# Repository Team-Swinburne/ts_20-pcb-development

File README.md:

# TS_20 PCB Development

This is the official repository for the PCB development of Team Swinburne FSAE 2020

## Installation & Usage

## Contributing
Pull requests are welcome. For major changes, please open an issue first to discuss what you would like to change.

Please make sure to update tests as appropriate.

## License
[MIT](https://choosealicense.com/licenses/mit/)

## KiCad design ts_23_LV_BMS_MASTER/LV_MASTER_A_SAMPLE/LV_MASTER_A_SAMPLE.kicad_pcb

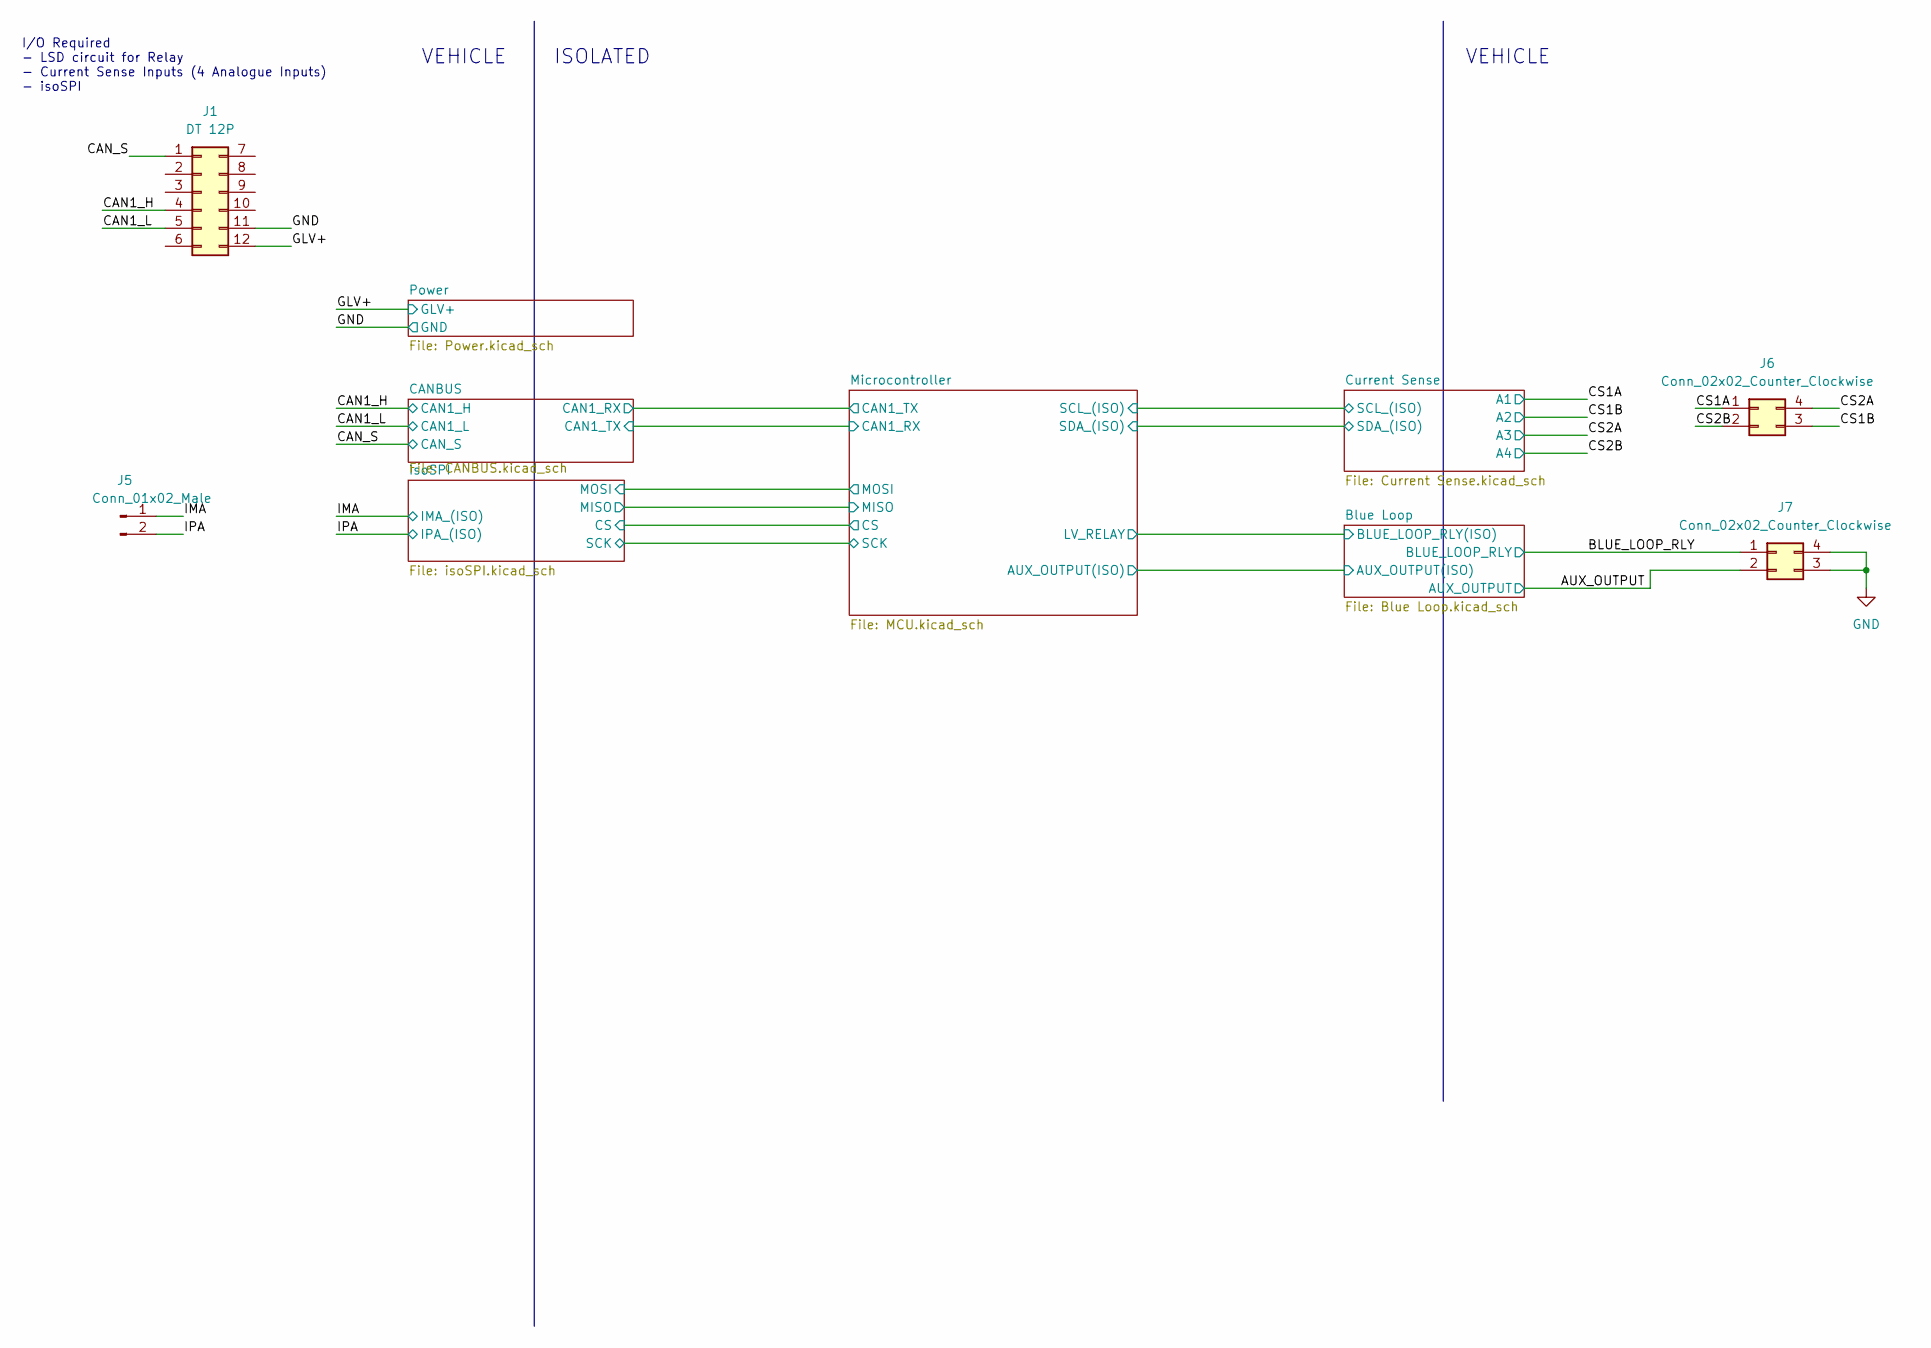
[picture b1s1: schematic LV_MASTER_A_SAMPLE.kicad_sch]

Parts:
J1: DT 12P; DT12-PCB PIN
J5: Conn_01x02_Male; Molex_Mini-Fit_Jr_5566-02A_2x01_P4.20mm_Vertical
J6, J7: Conn_02x02_Counter_Clockwise; Molex_Mini-Fit_Jr_5566-04A_2x02_P4.20mm_Vertical

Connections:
/AUX_OUTPUT: J7.2; also elsewhere on the board
/BLUE_LOOP_RLY: J7.1; also elsewhere on the board
/CAN1_H: J1.4; also elsewhere on the board
/CAN1_L: J1.5; also elsewhere on the board
/CS1A: J6.1; also elsewhere on the board
/CS1B: J6.3; also elsewhere on the board
/CS2A: J6.4; also elsewhere on the board
/CS2B: J6.2; also elsewhere on the board
/GLV+: J1.12; also elsewhere on the board
/IMA: J5.1; also elsewhere on the board
/IPA: J5.2; also elsewhere on the board

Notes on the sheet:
I/O Required - LSD circuit for Relay - Current Sense Inputs (4 Analogue Inputs) - isoSPI
VEHICLE
ISOLATED

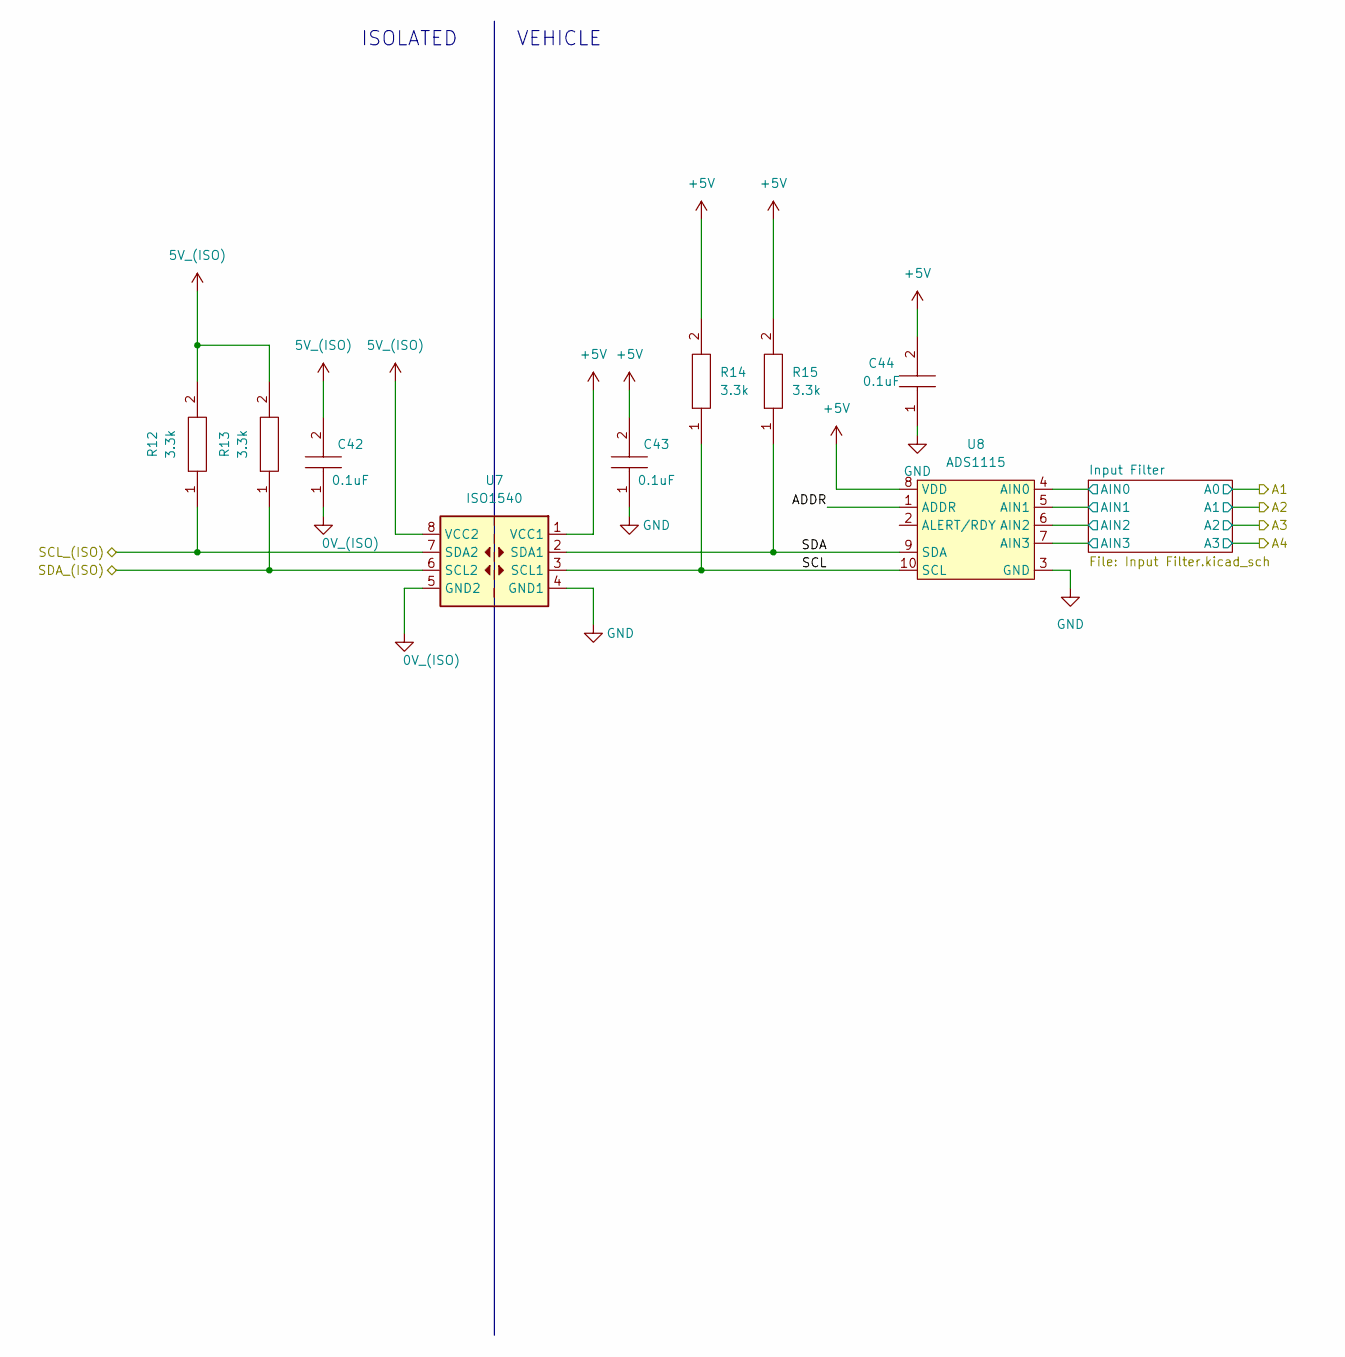
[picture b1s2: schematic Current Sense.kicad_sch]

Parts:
C42, C43, C44: 0.1uF; C_0603_1608Metric_Pad1.08x0.95mm_HandSolder; Manufacturer_Part_Number CC0805JRX7R8BB104; Mouser Part Number 603-CC805JRX7R8BB104
R12, R13, R14, R15: 3.3k; R_0603_1608Metric_Pad0.98x0.95mm_HandSolder; Manufacturer_Part_Number ERJP06F1000V
U7: ISO1540; SOIC-8_3.9x4.9mm_P1.27mm
U8: ADS1115; VSSOP-10_3x3mm_P0.5mm

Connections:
5V_(ISO): C42.2, R12.2, R13.2, U7.8 (VCC2); also elsewhere on the board
+5V: C43.2, C44.2, R14.2, R15.2, U7.1 (VCC1), U8.8 (VDD); also elsewhere on the board
/Current Sense/ADDR: U8.1 (ADDR)
/Current Sense/Input Filter/AIN0: U8.4 (AIN0); also elsewhere on the board
/Current Sense/Input Filter/AIN1: U8.5 (AIN1); also elsewhere on the board
/Current Sense/Input Filter/AIN2: U8.6 (AIN2); also elsewhere on the board
/Current Sense/Input Filter/AIN3: U8.7 (AIN3); also elsewhere on the board
/Current Sense/SCL: R14.1, U7.3 (SCL1), U8.10 (SCL)
/Current Sense/SDA: R15.1, U7.2 (SDA1), U8.9 (SDA)
/Microcontroller/SCL_(ISO): R12.1, U7.7 (SDA2); also elsewhere on the board
/Microcontroller/SDA_(ISO): R13.1, U7.6 (SCL2); also elsewhere on the board

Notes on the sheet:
ISOLATED
VEHICLE

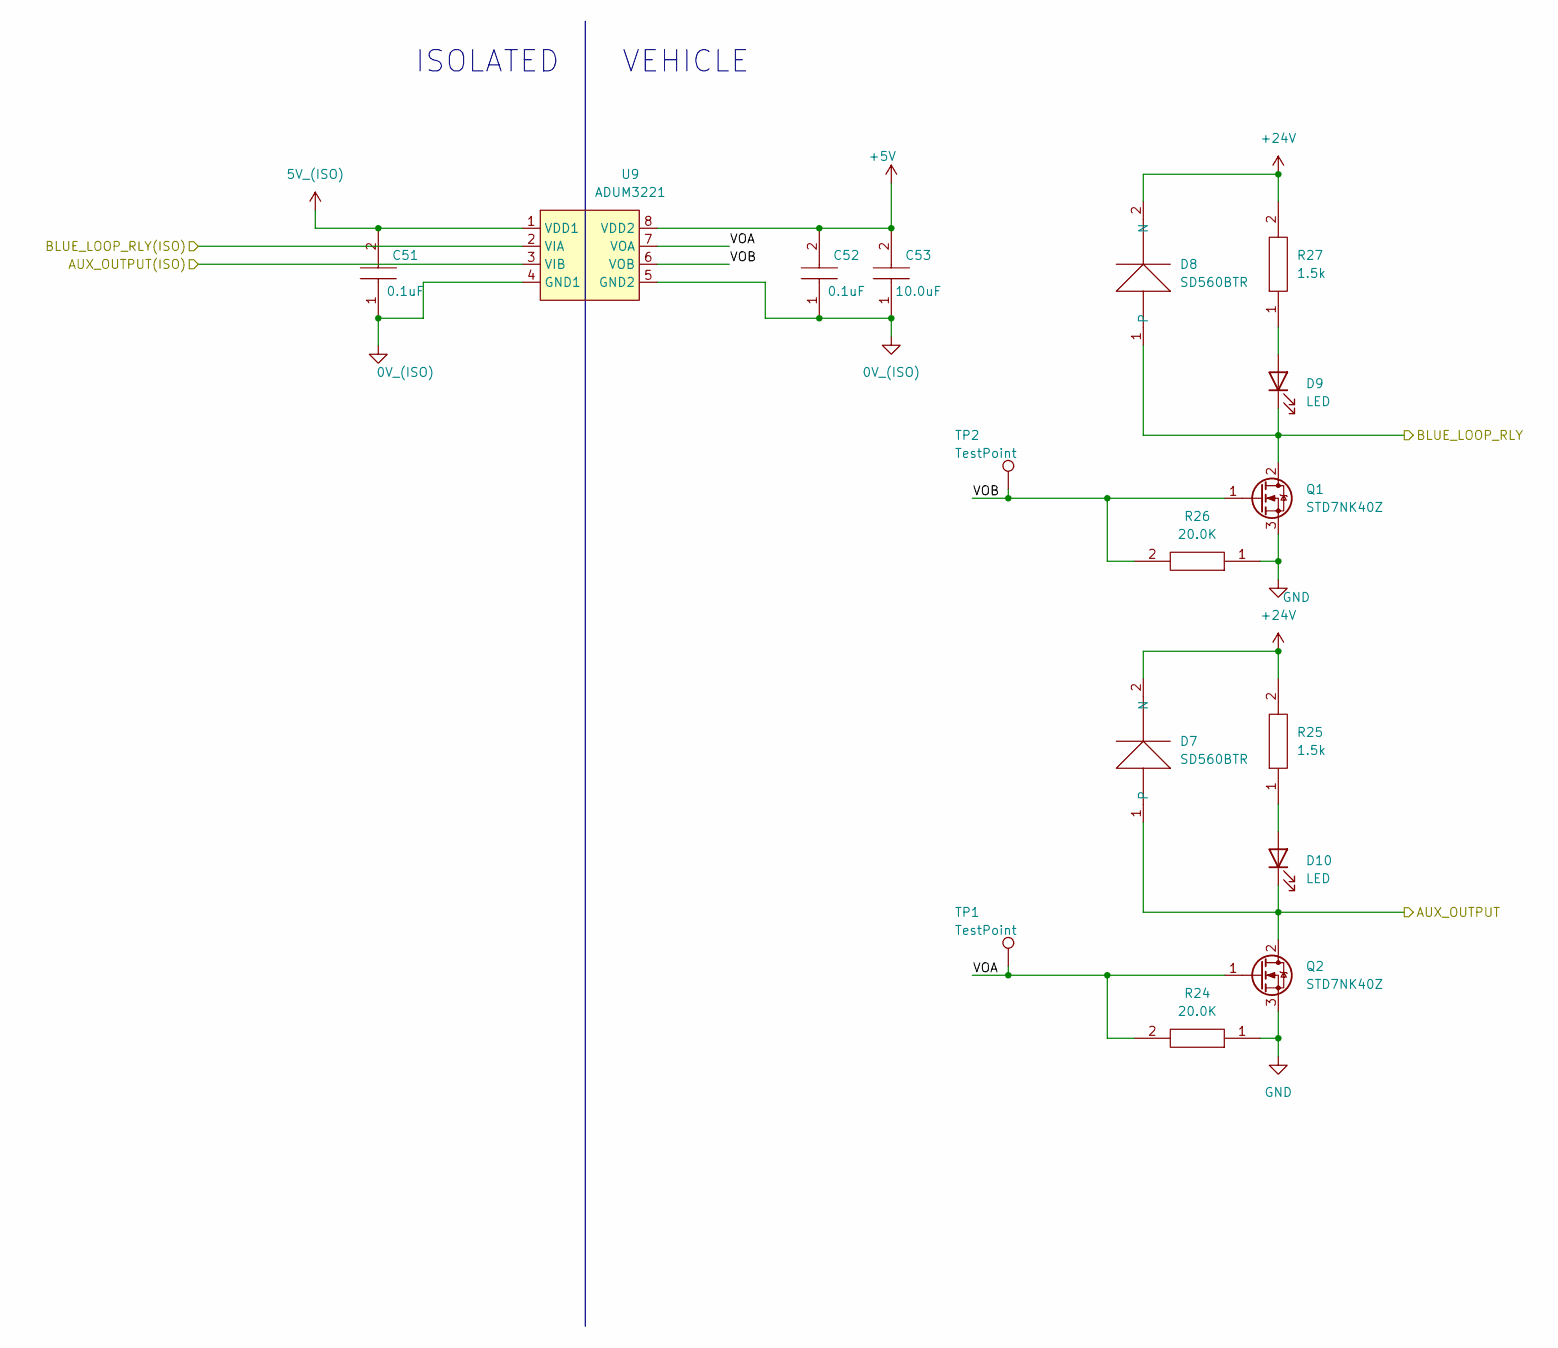
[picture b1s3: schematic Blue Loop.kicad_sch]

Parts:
C51, C52: 0.1uF; C_0603_1608Metric_Pad1.08x0.95mm_HandSolder; Manufacturer_Part_Number CC0805JRX7R8BB104; Mouser Part Number 603-CC805JRX7R8BB104
C53: 10.0uF; C_0603_1608Metric_Pad1.08x0.95mm_HandSolder; Manufacturer_Part_Number CC0805JRX7R8BB104; Mouser Part Number 603-CC805JRX7R8BB104
D7, D8: SD560BTR; D_SMB_Handsoldering
D9, D10: LED; LED_0805_2012Metric_Pad1.15x1.40mm_HandSolder
Q1, Q2: STD7NK40Z; TO-252-2
R24, R26: 20.0K; R_0603_1608Metric_Pad0.98x0.95mm_HandSolder; Manufacturer_Part_Number ERJP06F1000V
R25, R27: 1.5k; R_0603_1608Metric_Pad0.98x0.95mm_HandSolder; Manufacturer_Part_Number ERJP06F1000V
TP1, TP2: TestPoint; TestPoint_Pad_1.0x1.0mm
U9: ADUM3221; SOIC-8_3.9x4.9mm_P1.27mm

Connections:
5V_(ISO): C51.2, U9.1 (VDD1); also elsewhere on the board
+5V: C52.2, C53.2, U9.8 (VDD2); also elsewhere on the board
+24V: D7.2 (N), D8.2 (N), R25.2, R27.2; also elsewhere on the board
/AUX_OUTPUT: D7.1, D10.1 (K), Q2.2 (D); also elsewhere on the board
/BLUE_LOOP_RLY: D8.1, D9.1 (K), Q1.2 (D); also elsewhere on the board
/Blue Loop/AUX_OUTPUT(ISO): U9.3 (VIB); also elsewhere on the board
/Blue Loop/BLUE_LOOP_RLY(ISO): U9.2 (VIA); also elsewhere on the board
/Blue Loop/VOA: Q2.1 (G), R24.2, TP1.1, U9.7 (VOA); also elsewhere on the board
/Blue Loop/VOB: Q1.1 (G), R26.2, TP2.1, U9.6 (VOB); also elsewhere on the board
unnamed: D9.2 (A), R27.1
unnamed: D10.2 (A), R25.1

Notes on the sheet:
ISOLATED
VEHICLE

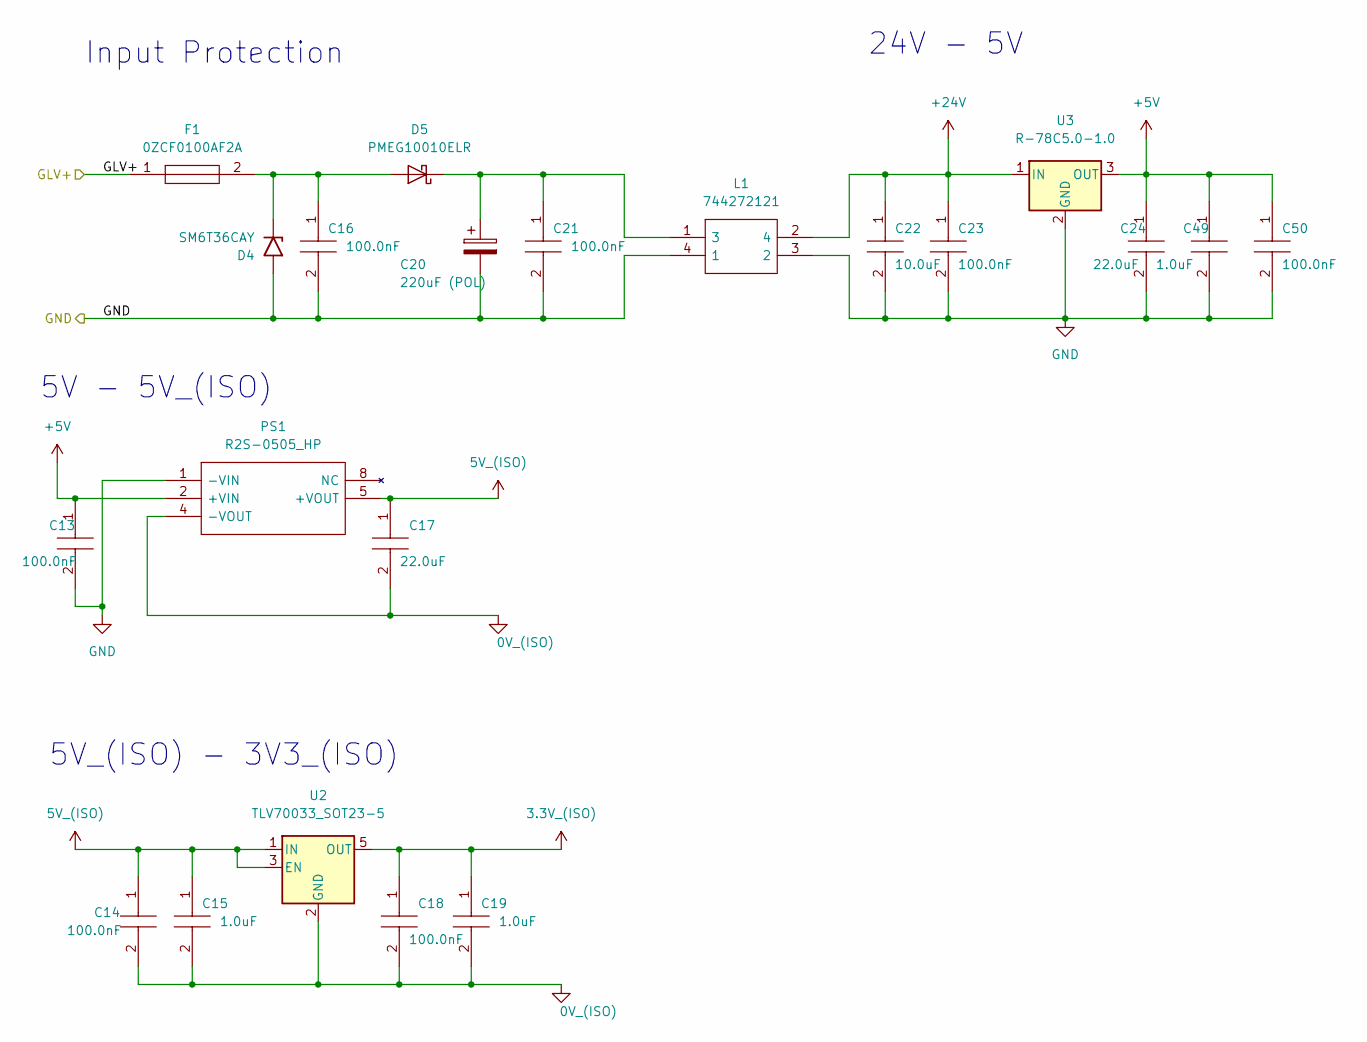
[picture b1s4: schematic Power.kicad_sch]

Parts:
C13, C14, C18, C21, C23, C50: 100.0nF; C_0603_1608Metric_Pad1.08x0.95mm_HandSolder; Manufacturer_Part_Number CC0805JRX7R8BB104; Mouser Part Number 603-CC805JRX7R8BB104
C15, C19, C49: 1.0uF; C_0603_1608Metric_Pad1.08x0.95mm_HandSolder; Manufacturer_Part_Number CC0805JRX7R8BB104; Mouser Part Number 603-CC805JRX7R8BB104
C16: 100.0nF; C_0805_2012Metric_Pad1.18x1.45mm_HandSolder; Manufacturer_Part_Number CC0805JRX7R8BB104; Mouser Part Number 603-CC805JRX7R8BB104
C17, C24: 22.0uF; C_0805_2012Metric_Pad1.18x1.45mm_HandSolder; Manufacturer_Part_Number CC0805JRX7R8BB104; Mouser Part Number 603-CC805JRX7R8BB104
C20: 220uF (POL); C_0805_2012Metric_Pad1.18x1.45mm_HandSolder
C22: 10.0uF; C_0603_1608Metric_Pad1.08x0.95mm_HandSolder; Manufacturer_Part_Number CC0805JRX7R8BB104; Mouser Part Number 603-CC805JRX7R8BB104
D4: SM6T36CAY; D_SMB
D5: PMEG10010ELR; Nexperia_CFP3_SOD-123W
F1: 0ZCF0100AF2A; FUSC7451X170N; Manufacturer_Part_Number 0ZCF0100AF2A; Mouser Part Number 530-0ZCF0100AF2A
L1: 744272121; WE-SL575; Manufacturer_Part_Number 744272121; Mouser Part Number 710-744272121
PS1: R2S-0505_HP; R2S0505HP; Manufacturer_Part_Number R2S-0505/HP; Mouser Part Number 919-R2S-0505HP
U2: TLV70033_SOT23-5; SOT-23-5
U3: R-78C5.0-1.0; Converter_DCDC_RECOM_R-78E-0.5_THT

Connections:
3.3V_(ISO): C18.1, C19.1, U2.5 (OUT); also elsewhere on the board
5V_(ISO): C14.1, C15.1, C17.1, PS1.5 (+VOUT), U2.1 (IN), U2.3 (EN); also elsewhere on the board
+5V: C13.1, C24.1, C49.1, C50.1, PS1.2 (+VIN), U3.3 (OUT); also elsewhere on the board
+24V: C22.1, C23.1, L1.2 (4), U3.1 (IN); also elsewhere on the board
/GLV+: F1.1; also elsewhere on the board
unnamed: C16.1, D4.1 (A1), D5.2 (A), F1.2
unnamed: C20.1, C21.1, D5.1 (K), L1.1 (3)

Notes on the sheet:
5V_(ISO) - 3V3_(ISO)
Input Protection
5V - 5V_(ISO)
24V - 5V

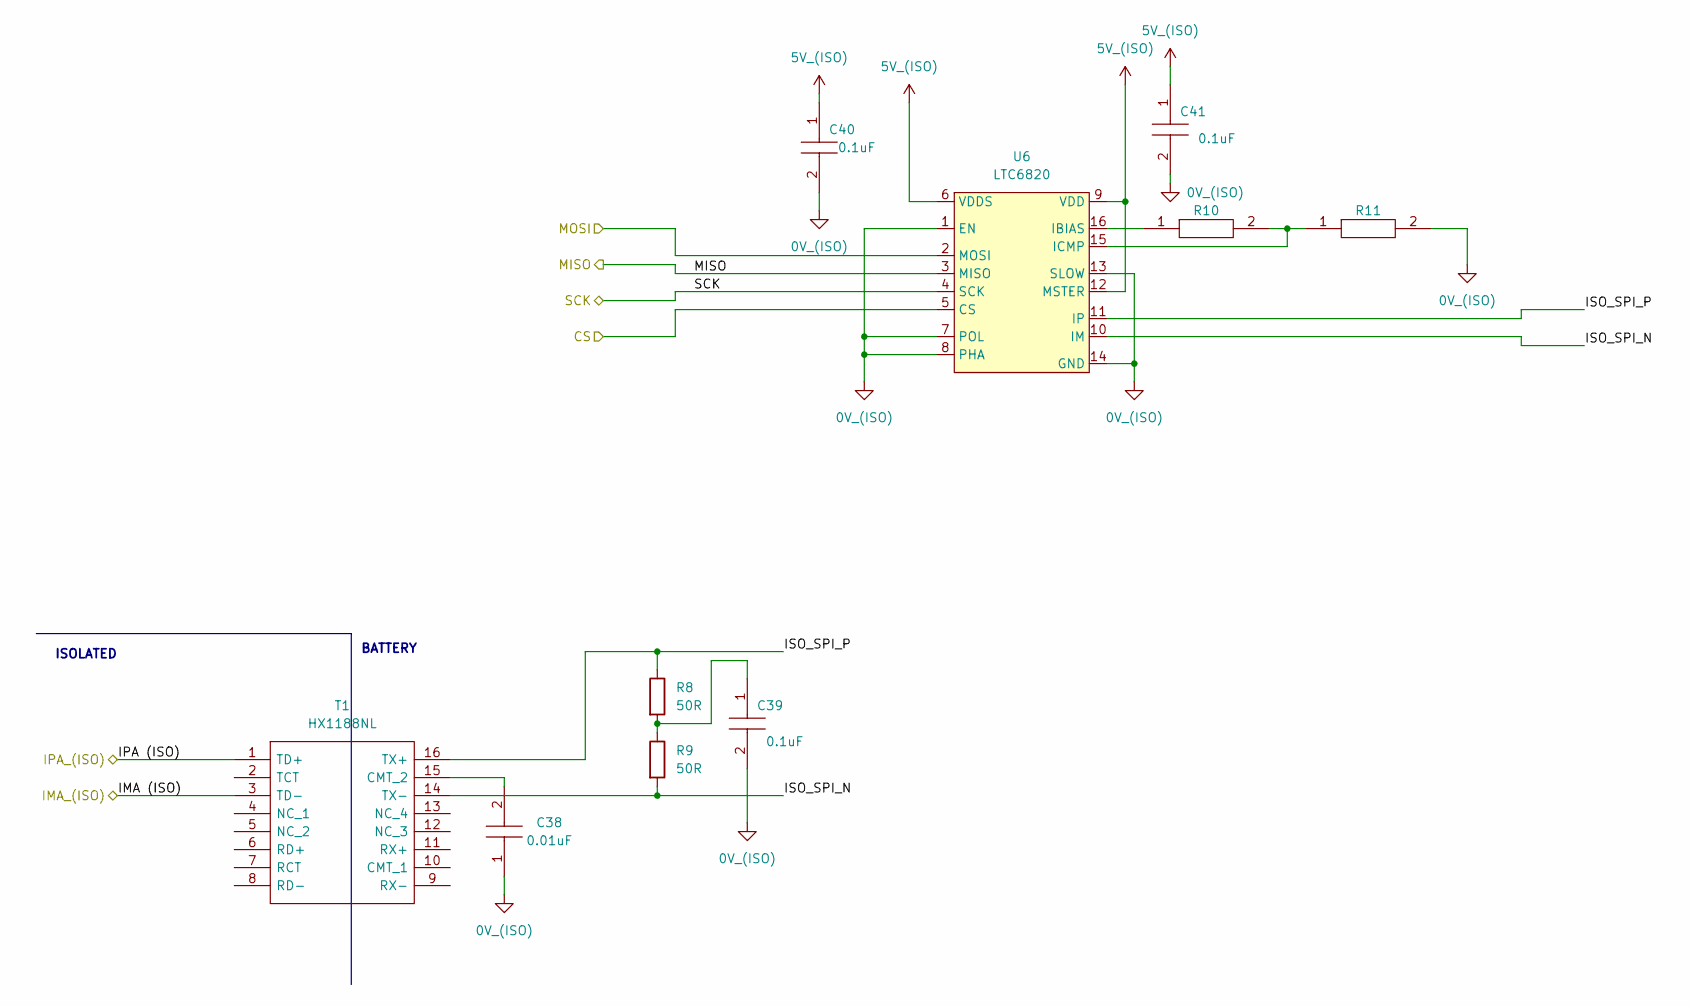
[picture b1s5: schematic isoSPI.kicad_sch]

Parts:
C38: 0.01uF; C_0603_1608Metric_Pad1.08x0.95mm_HandSolder; Manufacturer_Part_Number CC0805JRX7R9BB103
C39, C40, C41: 0.1uF; C_0603_1608Metric_Pad1.08x0.95mm_HandSolder; Manufacturer_Part_Number CC0805JRX7R8BB104; Mouser Part Number 603-CC805JRX7R8BB104
R8, R9: 50R; R_0603_1608Metric_Pad0.98x0.95mm_HandSolder
R10, R11: ERJP06F1000V; R_0603_1608Metric_Pad0.98x0.95mm_HandSolder; Manufacturer_Part_Number ERJP06F1000V
T1: HX1188NL; SOIC127P940X597-16N; Manufacturer_Part_Number HX1188NL; Mouser Part Number 673-HX1188NL
U6: LTC6820; MSOP-16_3x4.039mm_P0.5mm

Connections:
5V_(ISO): C40.1, C41.1, U6.6 (VDDS), U6.9 (VDD), U6.12 (MSTER); also elsewhere on the board
/IMA: T1.3 (TD-); also elsewhere on the board
/IPA: T1.1 (TD+); also elsewhere on the board
/Microcontroller/CS: U6.5 (CS); also elsewhere on the board
/Microcontroller/MISO: U6.3 (MISO); also elsewhere on the board
/Microcontroller/MOSI: U6.2 (MOSI); also elsewhere on the board
/Microcontroller/SCK: U6.4 (SCK); also elsewhere on the board
/isoSPI/ISO_SPI_N: R9.2, T1.14 (TX-), U6.10 (IM)
/isoSPI/ISO_SPI_P: R8.1, T1.16 (TX+), U6.11 (IP)
unnamed: C38.2, T1.15 (CMT_2)
unnamed: C39.1, R8.2, R9.1
unnamed: R10.1, U6.16 (IBIAS)
unnamed: R10.2, R11.1, U6.15 (ICMP)

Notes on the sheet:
ISOLATED
BATTERY

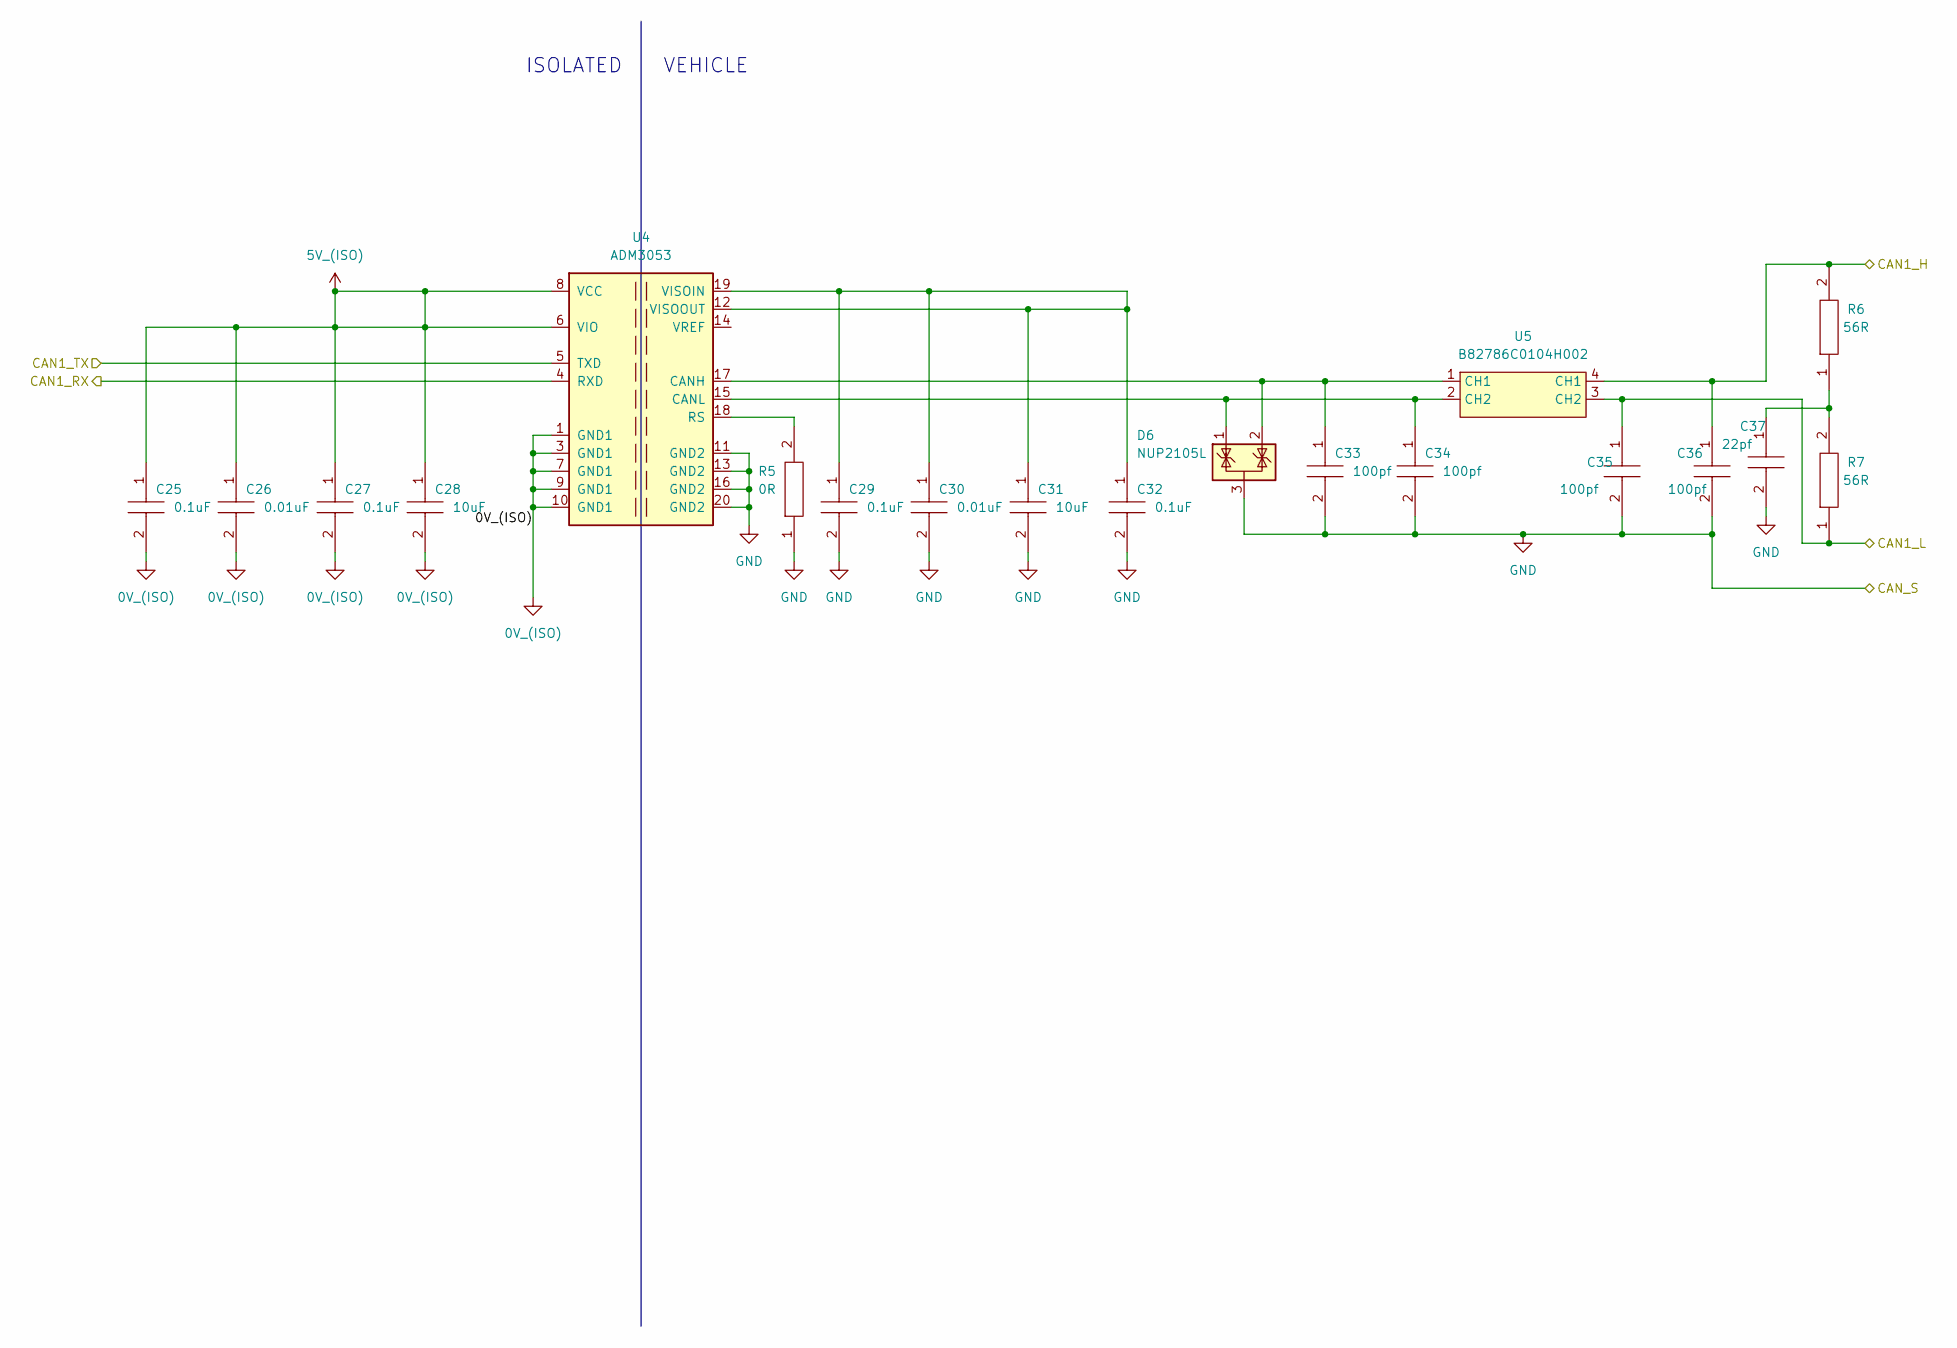
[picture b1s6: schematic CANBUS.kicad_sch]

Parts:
C25, C27, C29, C32: 0.1uF; C_0603_1608Metric_Pad1.08x0.95mm_HandSolder; Manufacturer_Part_Number CC0805JRX7R8BB104; Mouser Part Number 603-CC805JRX7R8BB104
C26, C30: 0.01uF; C_0603_1608Metric_Pad1.08x0.95mm_HandSolder; Manufacturer_Part_Number CC0805JRX7R8BB104; Mouser Part Number 603-CC805JRX7R8BB104
C28, C31: 10uF; C_0603_1608Metric_Pad1.08x0.95mm_HandSolder; Manufacturer_Part_Number CC0805JRX7R8BB104; Mouser Part Number 603-CC805JRX7R8BB104
C33, C34, C35, C36: 100pf; C_0603_1608Metric_Pad1.08x0.95mm_HandSolder; Manufacturer_Part_Number CC0805JRX7R8BB104; Mouser Part Number 603-CC805JRX7R8BB104
C37: 22pf; C_0603_1608Metric_Pad1.08x0.95mm_HandSolder; Manufacturer_Part_Number CC0805JRX7R8BB104; Mouser Part Number 603-CC805JRX7R8BB104
D6: NUP2105L; SOT-23
R5: 0R; R_0603_1608Metric_Pad0.98x0.95mm_HandSolder; Manufacturer_Part_Number ERJP06F1000V
R6, R7: 56R; R_0603_1608Metric_Pad0.98x0.95mm_HandSolder; Manufacturer_Part_Number ERJP06F1000V
U4: ADM3053; SOIC-20W_7.5x12.8mm_P1.27mm
U5: B82786C0104H002

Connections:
5V_(ISO): C25.1, C26.1, C27.1, C28.1, U4.6 (VIO), U4.8 (VCC); also elsewhere on the board
/CAN1_H: C36.1, R6.2, U5.4 (CH1); also elsewhere on the board
/CAN1_L: C35.1, R7.1, U5.3 (CH2); also elsewhere on the board
/CANBUS/CAN1_RX: U4.4 (RXD); also elsewhere on the board
/CANBUS/CAN1_TX: U4.5 (TXD); also elsewhere on the board
unnamed: C29.1, C30.1, C31.1, C32.1, U4.12 (VISOOUT), U4.19 (VISOIN)
unnamed: C33.1, D6.2 (K), U4.17 (CANH), U5.1 (CH1)
unnamed: C34.1, D6.1 (K), U4.15 (CANL), U5.2 (CH2)
unnamed: C37.1, R6.1, R7.2
unnamed: R5.2, U4.18 (RS)

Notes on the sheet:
VEHICLE
ISOLATED

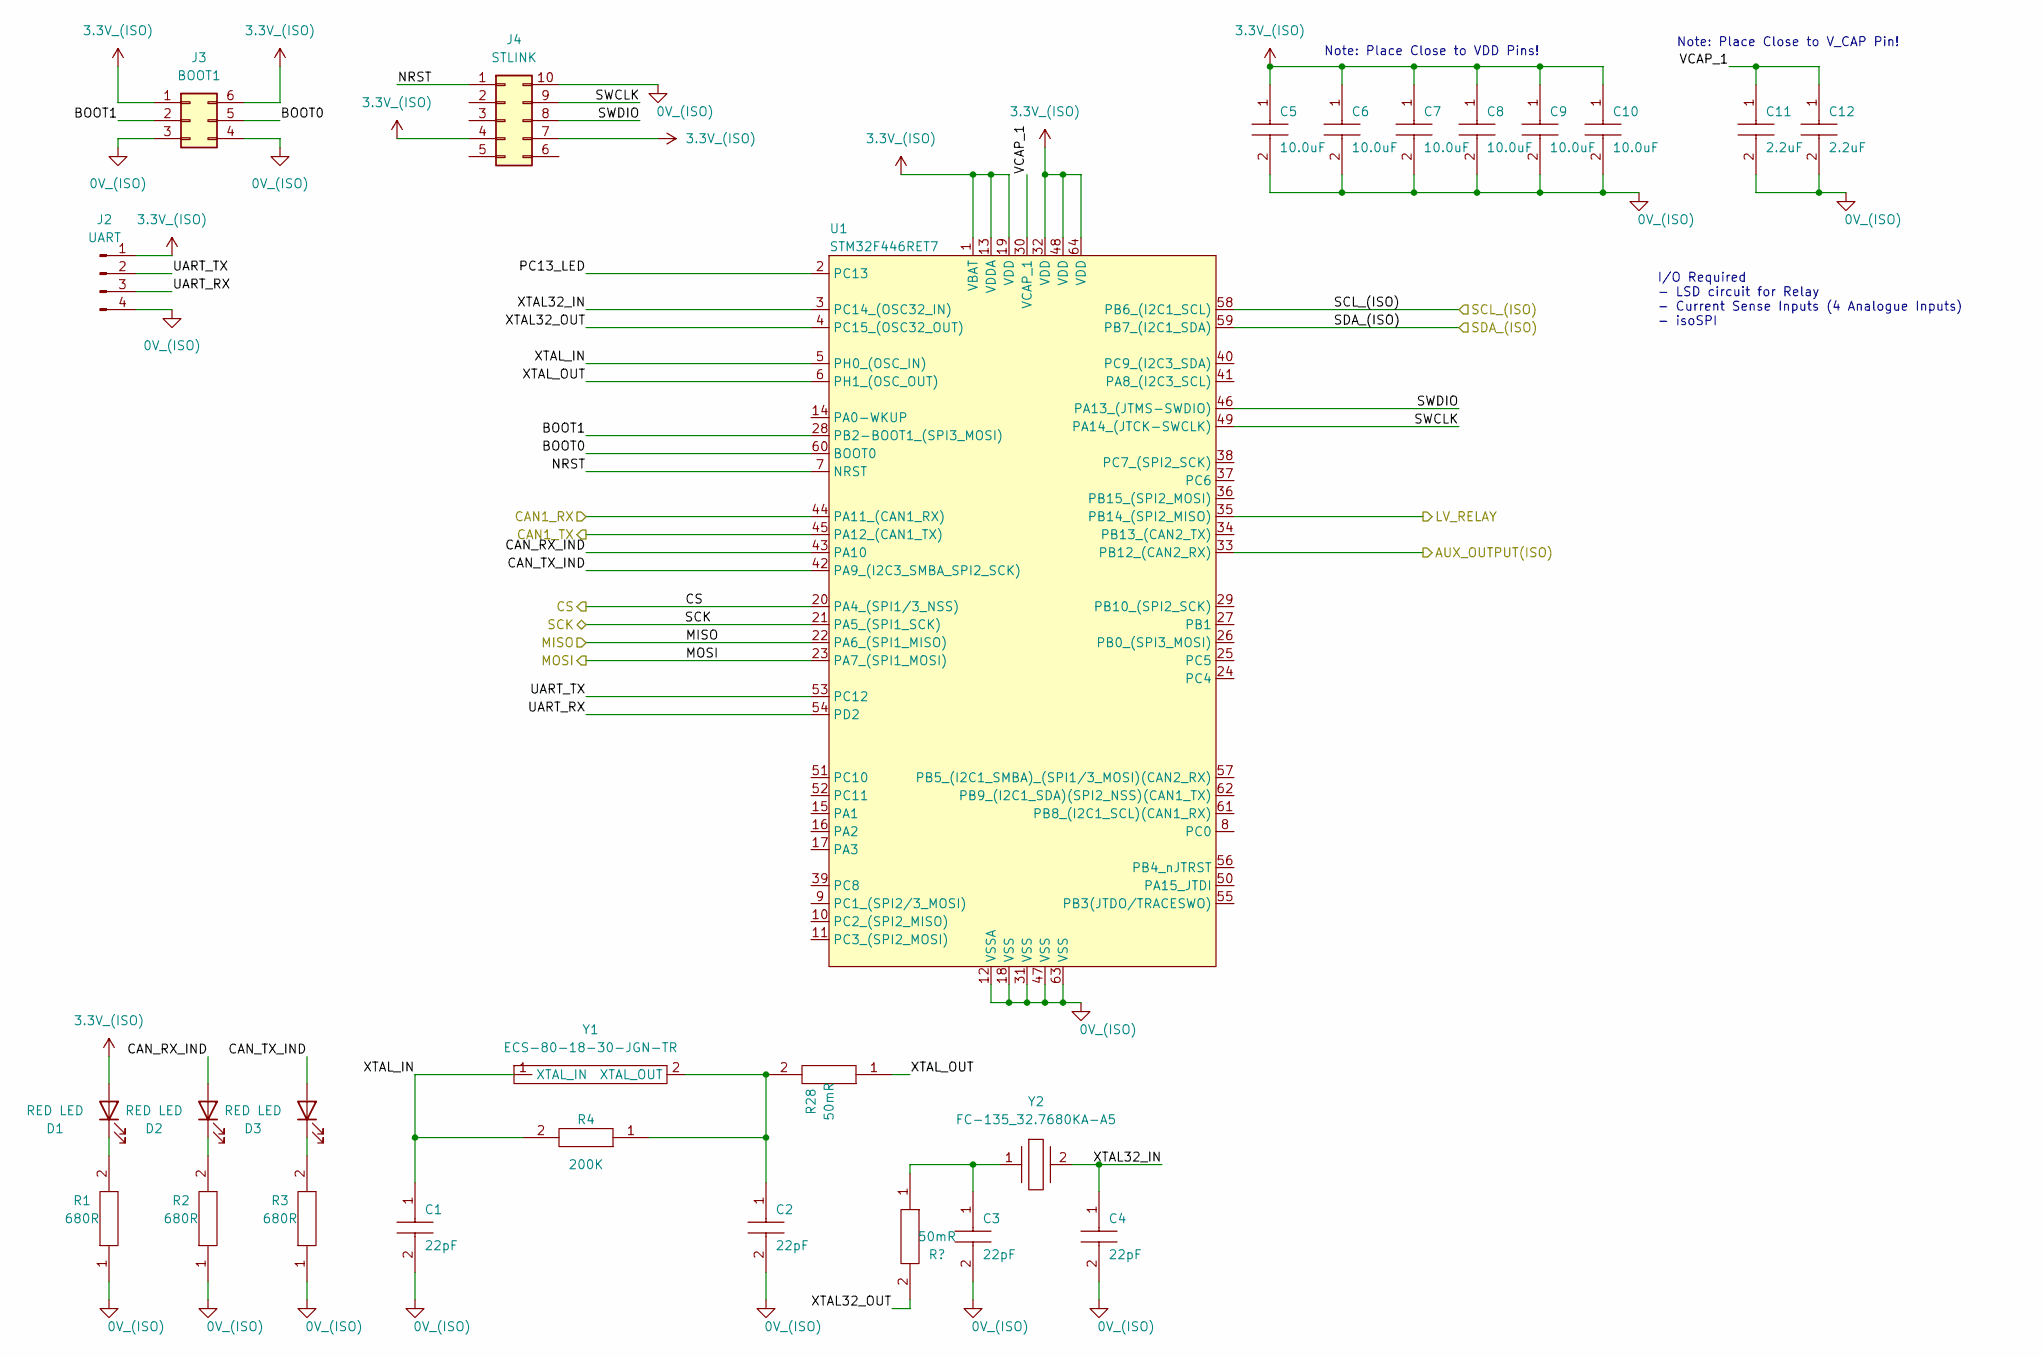
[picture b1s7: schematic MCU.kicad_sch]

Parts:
C1, C2, C3, C4: 22pF; C_0603_1608Metric_Pad1.08x0.95mm_HandSolder; Manufacturer_Part_Number CC0805JRX7R8BB104; Mouser Part Number 603-CC805JRX7R8BB104
C5, C6, C7, C8, C9, C10: 10.0uF; C_0603_1608Metric_Pad1.08x0.95mm_HandSolder; Manufacturer_Part_Number CC0805JRX7R8BB104; Mouser Part Number 603-CC805JRX7R8BB104
C11, C12: 2.2uF; C_0603_1608Metric_Pad1.08x0.95mm_HandSolder; Manufacturer_Part_Number CC0805JRX7R8BB104; Mouser Part Number 603-CC805JRX7R8BB104
D1, D2, D3: RED LED; C_0805_2012Metric_Pad1.18x1.45mm_HandSolder
J2: UART; PinHeader_1x04_P2.54mm_Vertical
J3: BOOT1; PinSocket_2x03_P2.54mm_Vertical
J4: STLINK; PinSocket_2x05_P2.54mm_Vertical_SMD
R1, R2, R3: 680R; R_0603_1608Metric_Pad0.98x0.95mm_HandSolder; Manufacturer_Part_Number ERJP06F1000V
R4: 200K; R_0603_1608Metric_Pad0.98x0.95mm_HandSolder; Manufacturer_Part_Number ERJP06F1000V
R28: 50mR; R_0603_1608Metric_Pad0.98x0.95mm_HandSolder; Manufacturer_Part_Number ERJP06F1000V
U1: STM32F446RET7; LQFP-64_10x10mm_P0.5mm
Y1: ECS-80-18-30-JGN-TR
Y2: FC-135_32.7680KA-A5; FC135327680KAA5; Manufacturer_Part_Number FC-135 32.7680KA-A5; Mouser Part Number 732-532.7680KA-A5

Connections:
3.3V_(ISO): C5.1, C6.1, C7.1, C8.1, C9.1, C10.1, D1.2 (A), J2.1, J3.1, J3.6, J4.4, J4.7, U1.1 (VBAT), U1.13 (VDDA), U1.19 (VDD), U1.32 (VDD), U1.48 (VDD), U1.64 (VDD); also elsewhere on the board
/Blue Loop/AUX_OUTPUT(ISO): U1.33 (PB12_(CAN2_RX)); also elsewhere on the board
/Blue Loop/BLUE_LOOP_RLY(ISO): U1.35 (PB14_(SPI2_MISO)); also elsewhere on the board
/CANBUS/CAN1_RX: U1.45 (PA12_(CAN1_TX)); also elsewhere on the board
/CANBUS/CAN1_TX: U1.44 (PA11_(CAN1_RX)); also elsewhere on the board
/Microcontroller/BOOT0: J3.5, U1.60 (BOOT0)
/Microcontroller/BOOT1: J3.2, U1.28 (PB2-BOOT1_(SPI3_MOSI))
/Microcontroller/CAN_RX_IND: D2.2 (A), U1.43 (PA10)
/Microcontroller/CAN_TX_IND: D3.2 (A), U1.42 (PA9_(I2C3_SMBA_SPI2_SCK))
/Microcontroller/CS: U1.20 (PA4_(SPI1/3_NSS)); also elsewhere on the board
/Microcontroller/MISO: U1.22 (PA6_(SPI1_MISO)); also elsewhere on the board
/Microcontroller/MOSI: U1.23 (PA7_(SPI1_MOSI)); also elsewhere on the board
/Microcontroller/NRST: J4.1, U1.7 (NRST)
/Microcontroller/PC13_LED: U1.2 (PC13)
/Microcontroller/SCK: U1.21 (PA5_(SPI1_SCK)); also elsewhere on the board
/Microcontroller/SCL_(ISO): U1.58 (PB6_(I2C1_SCL)); also elsewhere on the board
/Microcontroller/SDA_(ISO): U1.59 (PB7_(I2C1_SDA)); also elsewhere on the board
/Microcontroller/SWCLK: J4.9, U1.49 (PA14_(JTCK-SWCLK))
/Microcontroller/SWDIO: J4.8, U1.46 (PA13_(JTMS-SWDIO))
/Microcontroller/UART_RX: J2.3, U1.54 (PD2)
/Microcontroller/UART_TX: J2.2, U1.53 (PC12)
/Microcontroller/VCAP_1: C11.1, C12.1, U1.30 (VCAP_1)
/Microcontroller/XTAL32_IN: C4.1, U1.3 (PC14_(OSC32_IN)), Y2.2
/Microcontroller/XTAL32_OUT: U1.4 (PC15_(OSC32_OUT)); also elsewhere on the board
/Microcontroller/XTAL_IN: C1.1, R4.2, U1.5 (PH0_(OSC_IN)), Y1.1 (XTAL_IN)
/Microcontroller/XTAL_OUT: R28.1, U1.6 (PH1_(OSC_OUT))
unnamed: C2.1, R4.1, R28.2, Y1.2 (XTAL_OUT)
unnamed 52: C3.1, Y2.1; also elsewhere on the board
unnamed: D1.1 (K), R1.2
unnamed: D2.1 (K), R2.2
unnamed: D3.1 (K), R3.2

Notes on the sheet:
I/O Required - LSD circuit for Relay - Current Sense Inputs (4 Analogue Inputs) - isoSPI
Note: Place Close to VDD Pins!
Note: Place Close to V_CAP Pin!
